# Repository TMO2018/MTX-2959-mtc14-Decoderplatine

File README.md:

# MTX-2959-mtc14-Decoderplatine
Minitrix 2959 Decoderplatine mit mtc14-Schnittstelle

In diesem Projekt ist eine Digitalplatine mit mtc14-Digitalschnittstelle für die Minitrix Diesellok BR 216 090-1 (2959) beschrieben.
Diese Platine ersetzt 1:1 die vorhandene Platine und bietet zusätzlich eine Möglichkeit zum Anschluß von LED’s für Front- und Rückbeleuchtung.

Die Gerberdateien zur Herstellung der Platine befinden sich im kicad-Ordner (zip-Datei).

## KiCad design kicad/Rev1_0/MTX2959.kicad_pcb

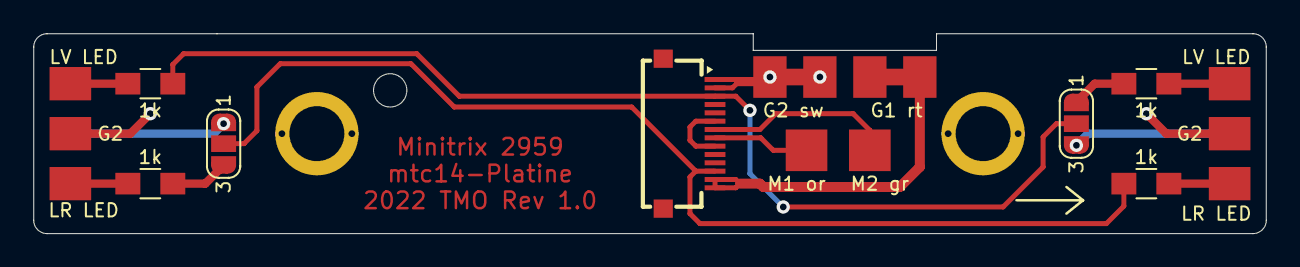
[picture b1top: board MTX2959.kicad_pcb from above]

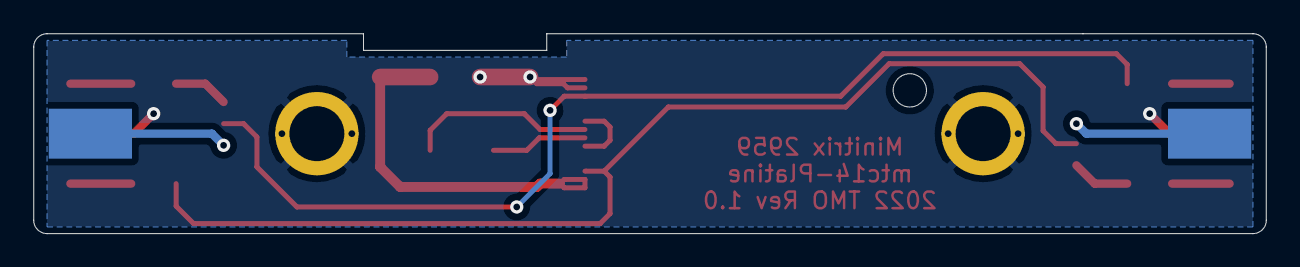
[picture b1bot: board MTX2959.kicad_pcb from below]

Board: 2 copper layers, 74.0 x 12.0 mm, 23 parts (2 on the bottom side), 15 nets.

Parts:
H1, H2: Chassis; MountingHole_3.3mm_Pad_5mm
J1: mtc14; FPC-SMD_14P-P0.5_HDGC_0.5K-QX-14PWB_HandSoldering_(mtc14)
J11, J12: G1 rt; Measurement_Point_Square-SMD-Pad_Small
J13, J14: G2 sw; Measurement_Point_Square-SMD-Pad_Small
J21: M1 or; Measurement_Point_Square-SMD-Pad_Small
J22: M2 gr; Measurement_Point_Square-SMD-Pad_Small
J31: LV Lampe vorne; Measurement_Point_Square-SMD-Pad_Big
J32, J44: LV LED; Measurement_Point_Square-SMD-Pad_Small
J33, J43: G2; Measurement_Point_Square-SMD-Pad_Small
J34, J42: LR LED; Measurement_Point_Square-SMD-Pad_Small
J41: LR Lampe hinten; Measurement_Point_Square-SMD-Pad_Big
JP1, JP2: SolderJumper_2_Open; SolderJumper-3_P1.3mm_Open_RoundedPad1.0x1.5mm_NumberLabels
R1, R2, R3, R4: 1k; R_0805_HandSoldering

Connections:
G1: J1.13, J1.14, J11.1, J12.1
G2: H1.1, H2.1, J1.1, J1.2, J13.1, J14.1, J33.1, J43.1
GND: J1.6, J1.9
LR: J1.12, JP2.2, R2.1
LV: J1.3, JP1.2, R4.1
M1: J1.8, J21.1
M2: J1.7, J22.1
unnamed: J31.1, JP1.3
unnamed: J32.1, R1.2
unnamed: J34.1, R2.2
unnamed: J41.1, JP2.1
unnamed: J42.1, R3.2
unnamed: J44.1, R4.2
unnamed: JP1.1, R1.1
unnamed: JP2.3, R3.1
